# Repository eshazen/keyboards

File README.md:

# Keyboard project(s)

<p>

## Status

All done, working!  Used QMK for the firmware.  
<br>See `my_84/qmk/eric_84/key` for modified
`keyboard.json` and `keymaps/default/keymap.c`.  
<br>See [README_QMK](README_QMK.md).

To change layout, edit `~/qmk_firmware/keyboards/eric_84_key/keymaps/default/keymap.c`.
Then re-flash with:

    qmk flash -kb eric_84_key -km default

(This can be done "live" as long as you have access to the Arduino reset button).

In summary, created the layout in KLE, generated the plate and case
geometry in `swillkb.com`, and the PCB using the `kbplacer` plugin for
KiCAD.  Firmware generated using `qmk`.

Waterjet cutter files for plate in `waterJet`.

## Tools Used:

* [KLE](https://www.keyboard-layout-editor.com)
* [Plate & Case Builder](http://builder.swillkb.com/) (from [github](https://github.com/vladantrhlik/Keyboard_case_generator?tab=readme-ov-file)).  This generates the DXF for the plate and stacked laser-cut case parts.
* [kbplacer plugin](https://github.com/adamws/kicad-kbplacer) for KiCAD layout

## References

* [PCB video](https://www.youtube.com/watch?v=u13yRbBiRYM&t=10s)
* [Case video](https://www.youtube.com/watch?v=NIIr19TdidY)
* [Building Keyboards with Lasers](https://kbd.news/Building-keyboards-with-lasers-2208.html)
* [Keyboard University](https://www.keyboard.university/)
* [Pro Micro up to 100 pins](https://golem.hu/guide/pro-micro/)

Also used 

## My 84 key

<ul>
    [{a:6},"Esc","F1","F2","F3","F4","F5","F6","F7","F8","F9","F10","F11","F12",{a:7},"PrtSc","Shell","Pause"],
    [{a:4},"~\n`","!\n1","@\n2","#\n3","$\n4","%\n5","^\n6","&\n7","*\n8","(\n9",")\n0","_\n-","+\n=",{a:6,w:2},"Backspace",{a:7},"Insert"],
    [{a:4,w:1.5},"Tab","Q","W","E","R","T","Y","U","I","O","P","{\n[","}\n]",{w:1.5},"|\n\\",{a:6},"Delete"],
    [{w:1.75},"Control",{a:4},"A","S","D","F","G","H","J","K","L",":\n;","\"\n'",{a:6,w:2.25},"Enter","Page Up"],
    [{w:2.25},"Shift",{a:4},"Z","X","C","V","B","N","M","<\n,",">\n.","?\n/",{a:6,w:1.75},"Shift",{a:7},"↑",{a:6},"Page Down"],
    [{a:7,w:1.25},"Home",{a:6,w:1.25},"Menu",{w:1.25},"Alt",{a:7,w:6.25},"",{a:6},"Alt","Fn",{a:7},"End","←","↓","→"]

Using [http://builder.swillkb.com/](http://builder.swillkb.com/).

``` text
    Switch type: MX
	Stab:  Cherry + Costar
	Case: Sandwich
	Holes 8, 4.5mm, 10mm
	Edge:  Top: 10, Left: 30, Right: 10, Bottom: 25
	Corners: 2mm
```
<br>DXFs in `...Case/case1`
<br>PCB in `...kb_test`

This was OK except that the opening in the 'top' was a little tight.
Enlarged the CAD file by .05" on all sides.

</ul>

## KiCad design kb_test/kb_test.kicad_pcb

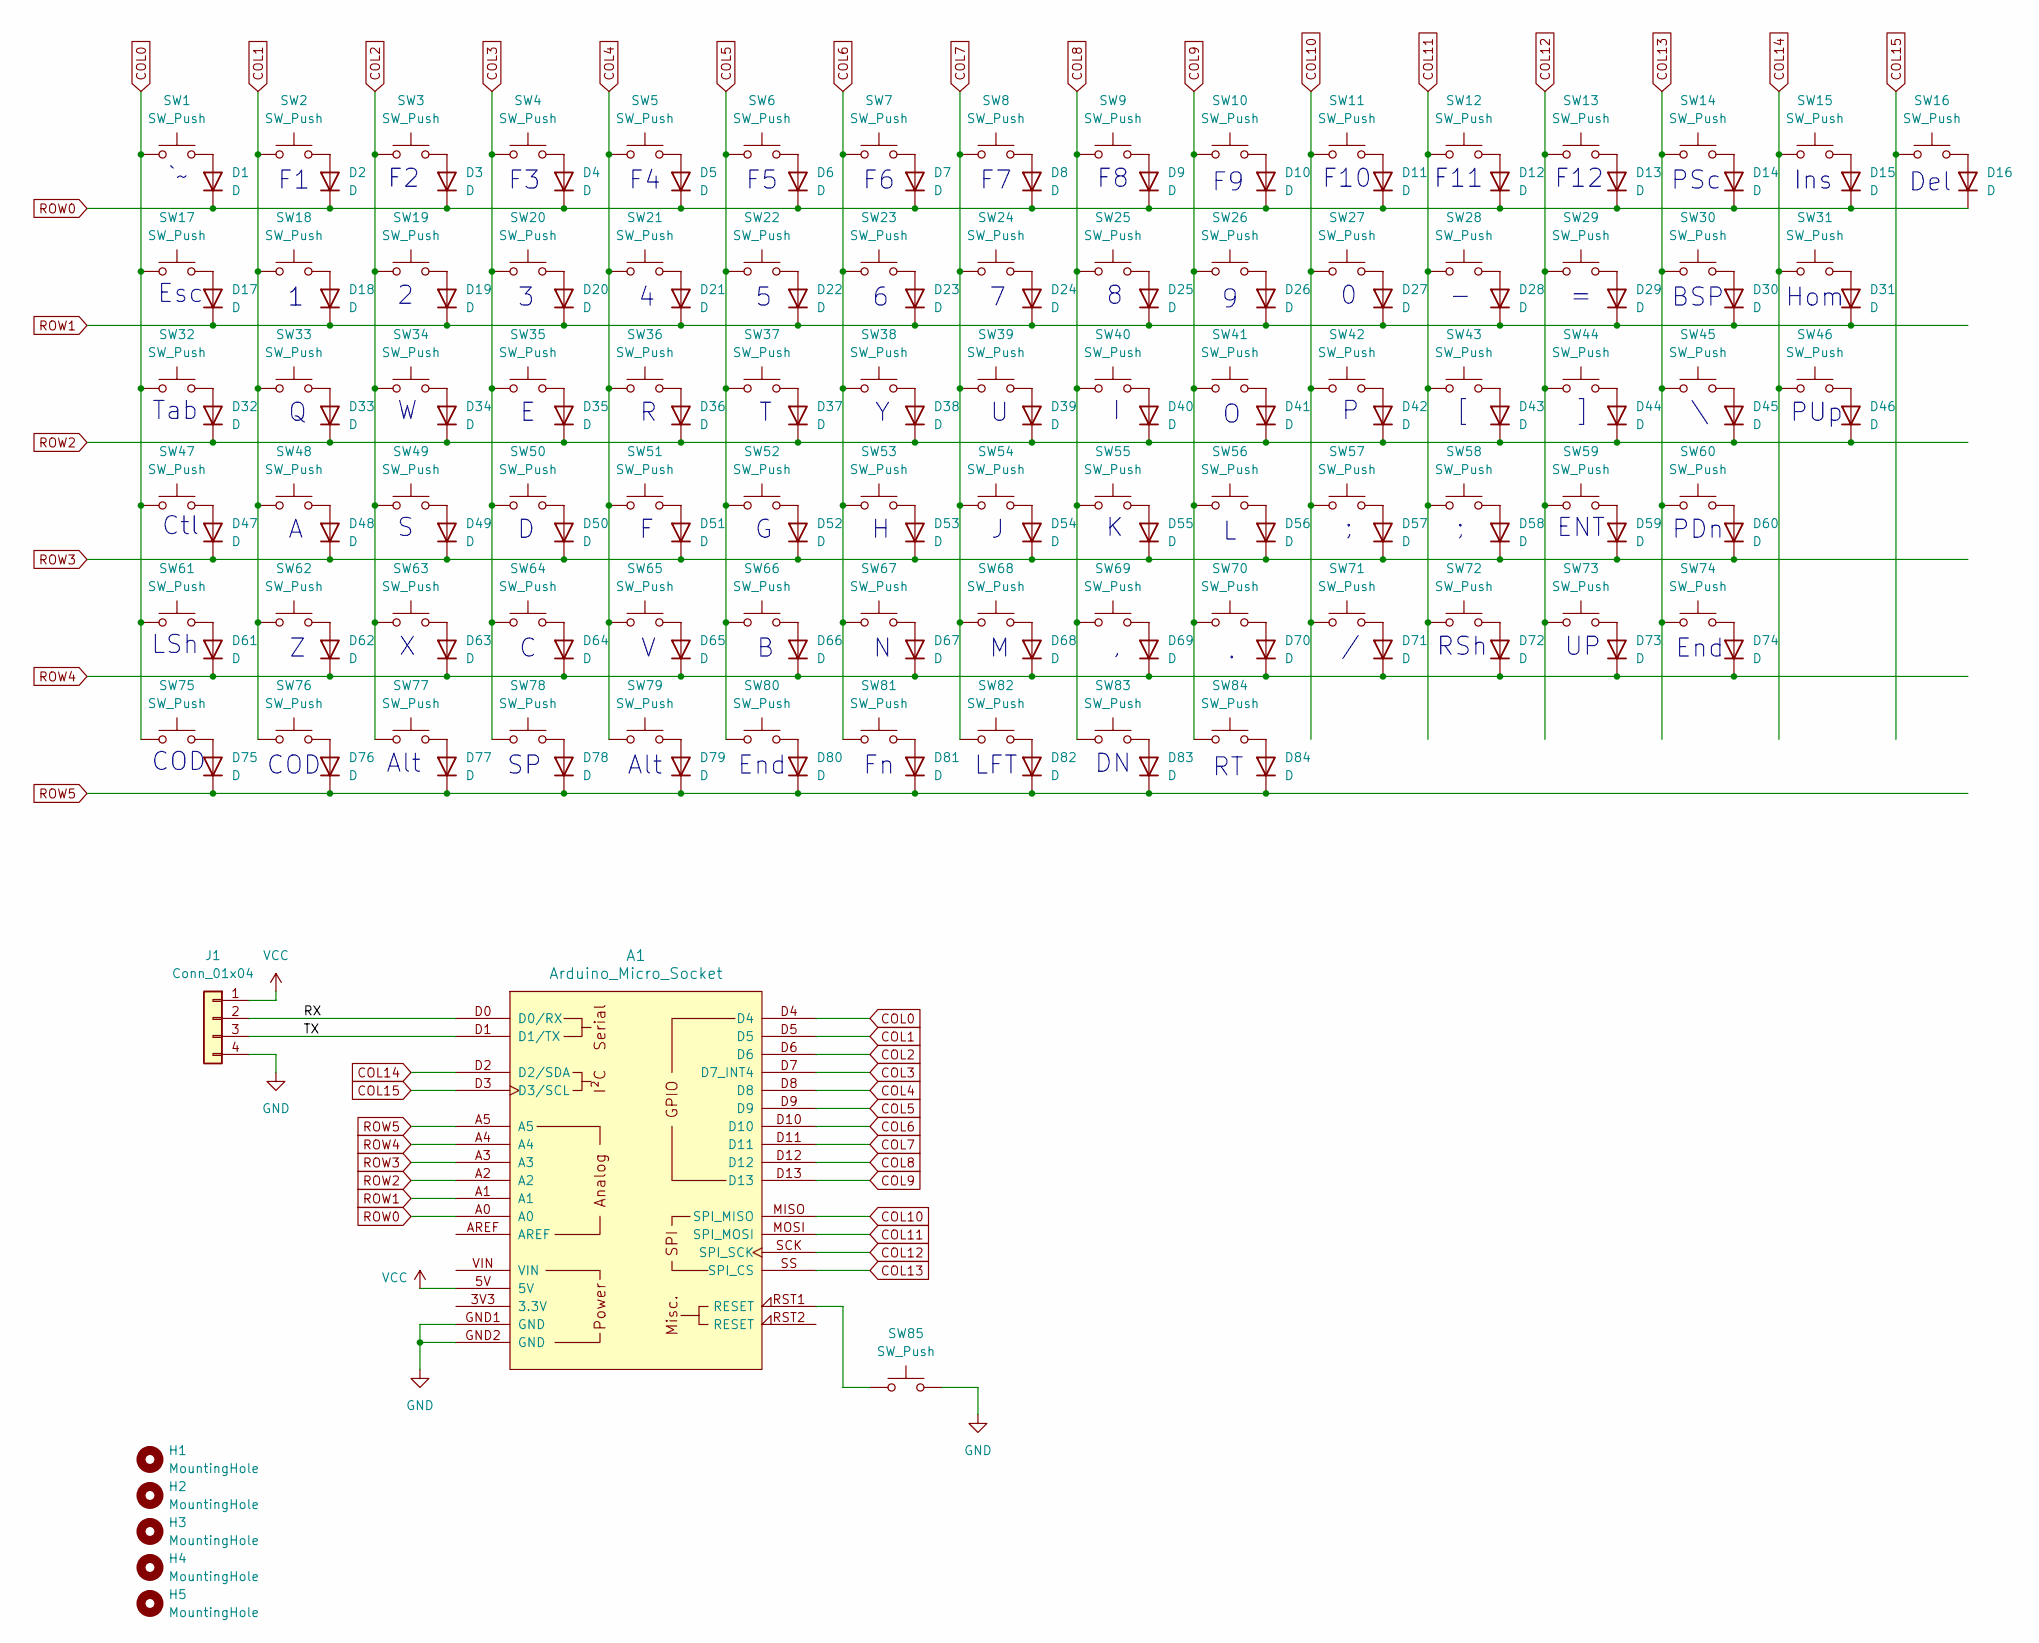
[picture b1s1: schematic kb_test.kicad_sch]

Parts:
A1: Arduino_Micro_Socket
D1, D2, D3, D4, D5, D6, D7, D8, D9, D10, D11, D12, D13, D14, D15, D16, D17, D18, D19, D20, D21, D22, D23, D24, D25, D26, D27, D28, D29, D30, D31, D32, D33, D34, D35, D36, D37, D38, D39, D40, D41, D42, D43, D44, D45, D46, D47, D48, D49, D50, D51, D52, D53, D54, D55, D56, D57, D58, D59, D60, D61, D62, D63, D64, D65, D66, D67, D68, D69, D70, D71, D72, D73, D74, D75, D76, D77, D78, D79, D80, D81, D82, D83, D84: D; D_DO-41_SOD81_P7.62mm_Horizontal
H1, H2, H3, H4, H5: MountingHole; MountingHole_4.3mm_M4
J1: Conn_01x04; PinHeader_1x04_P2.54mm_Vertical
SW1, SW2, SW3, SW4, SW5, SW6, SW7, SW8, SW9, SW10, SW11, SW12, SW13, SW14, SW15, SW16, SW17, SW18, SW19, SW20, SW21, SW22, SW23, SW24, SW25, SW26, SW27, SW28, SW29, SW30, SW31, SW32, SW33, SW34, SW35, SW36, SW37, SW38, SW39, SW40, SW41, SW42, SW43, SW44, SW45, SW46, SW47, SW48, SW49, SW50, SW51, SW52, SW53, SW54, SW55, SW56, SW57, SW58, SW59, SW60, SW61, SW62, SW63, SW64, SW65, SW66, SW67, SW68, SW69, SW70, SW71, SW72, SW73, SW74, SW75, SW76, SW77, SW78, SW79, SW80, SW81, SW82, SW83, SW84: SW_Push; SW_Cherry_MX_1.00u_PCB
SW85: SW_Push; SW_Tactile_Straight_KSA0Axx1LFTR

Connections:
/RX: A1.D0 (D0/RX), J1.2
/TX: A1.D1 (D1/TX), J1.3
COL0: A1.D4, SW1.1, SW17.1, SW32.1, SW47.1, SW61.1, SW75.1
COL1: A1.D5, SW2.1, SW18.1, SW33.1, SW48.1, SW62.1, SW76.1
COL2: A1.D6, SW3.1, SW19.1, SW34.1, SW49.1, SW63.1, SW77.1
COL3: A1.D7 (D7_INT4), SW4.1, SW20.1, SW35.1, SW50.1, SW64.1, SW78.1
COL4: A1.D8, SW5.1, SW21.1, SW36.1, SW51.1, SW65.1, SW79.1
COL5: A1.D9, SW6.1, SW22.1, SW37.1, SW52.1, SW66.1, SW80.1
COL6: A1.D10, SW7.1, SW23.1, SW38.1, SW53.1, SW67.1, SW81.1
COL7: A1.D11, SW8.1, SW24.1, SW39.1, SW54.1, SW68.1, SW82.1
COL8: A1.D12, SW9.1, SW25.1, SW40.1, SW55.1, SW69.1, SW83.1
COL9: A1.D13, SW10.1, SW26.1, SW41.1, SW56.1, SW70.1, SW84.1
COL10: A1.MISO (SPI_MISO), SW11.1, SW27.1, SW42.1, SW57.1, SW71.1
COL11: A1.MOSI (SPI_MOSI), SW12.1, SW28.1, SW43.1, SW58.1, SW72.1
COL12: A1.SCK (SPI_SCK), SW13.1, SW29.1, SW44.1, SW59.1, SW73.1
COL13: A1.SS (SPI_CS), SW14.1, SW30.1, SW45.1, SW60.1, SW74.1
COL14: A1.D2 (D2/SDA), SW15.1, SW31.1, SW46.1
COL15: A1.D3 (D3/SCL), SW16.1
GND: A1.GND1 (GND), A1.GND2 (GND), J1.4, SW85.2
unnamed: A1.RST1 (RESET), SW85.1
unnamed: D1.2 (A), SW1.2
unnamed: D2.2 (A), SW2.2
unnamed: D3.2 (A), SW3.2
unnamed: D4.2 (A), SW4.2
unnamed: D5.2 (A), SW5.2
unnamed: D6.2 (A), SW6.2
unnamed: D7.2 (A), SW7.2
unnamed: D8.2 (A), SW8.2
unnamed: D9.2 (A), SW9.2
unnamed: D10.2 (A), SW10.2
unnamed: D11.2 (A), SW11.2
unnamed: D12.2 (A), SW12.2
unnamed: D13.2 (A), SW13.2
unnamed: D14.2 (A), SW14.2
unnamed: D15.2 (A), SW15.2
unnamed: D16.2 (A), SW16.2
unnamed: D17.2 (A), SW17.2
unnamed: D18.2 (A), SW18.2
unnamed: D19.2 (A), SW19.2
unnamed: D20.2 (A), SW20.2
unnamed: D21.2 (A), SW21.2
unnamed: D22.2 (A), SW22.2
unnamed: D23.2 (A), SW23.2
unnamed: D24.2 (A), SW24.2
unnamed: D25.2 (A), SW25.2
unnamed: D26.2 (A), SW26.2
unnamed: D27.2 (A), SW27.2
unnamed: D28.2 (A), SW28.2
unnamed: D29.2 (A), SW29.2
unnamed: D30.2 (A), SW30.2
unnamed: D31.2 (A), SW31.2
unnamed: D32.2 (A), SW32.2
unnamed: D33.2 (A), SW33.2
unnamed: D34.2 (A), SW34.2
unnamed: D35.2 (A), SW35.2
unnamed: D36.2 (A), SW36.2
unnamed: D37.2 (A), SW37.2
unnamed: D38.2 (A), SW38.2
unnamed: D39.2 (A), SW39.2
unnamed: D40.2 (A), SW40.2
unnamed: D41.2 (A), SW41.2
unnamed: D42.2 (A), SW42.2
unnamed: D43.2 (A), SW43.2
unnamed: D44.2 (A), SW44.2
unnamed: D45.2 (A), SW45.2
unnamed: D46.2 (A), SW46.2
unnamed: D47.2 (A), SW47.2
unnamed: D48.2 (A), SW48.2
unnamed: D49.2 (A), SW49.2
unnamed: D50.2 (A), SW50.2
unnamed: D51.2 (A), SW51.2
unnamed: D52.2 (A), SW52.2
unnamed: D53.2 (A), SW53.2
unnamed: D54.2 (A), SW54.2
unnamed: D55.2 (A), SW55.2
unnamed: D56.2 (A), SW56.2
unnamed: D57.2 (A), SW57.2
unnamed: D58.2 (A), SW58.2
unnamed: D59.2 (A), SW59.2
unnamed: D60.2 (A), SW60.2
unnamed: D61.2 (A), SW61.2
unnamed: D62.2 (A), SW62.2
unnamed: D63.2 (A), SW63.2
unnamed: D64.2 (A), SW64.2
unnamed: D65.2 (A), SW65.2
unnamed: D66.2 (A), SW66.2
unnamed: D67.2 (A), SW67.2
unnamed: D68.2 (A), SW68.2
unnamed: D69.2 (A), SW69.2
unnamed: D70.2 (A), SW70.2
unnamed: D71.2 (A), SW71.2
unnamed: D72.2 (A), SW72.2
unnamed: D73.2 (A), SW73.2
unnamed: D74.2 (A), SW74.2
unnamed: D75.2 (A), SW75.2
unnamed: D76.2 (A), SW76.2
unnamed: D77.2 (A), SW77.2
unnamed: D78.2 (A), SW78.2
unnamed: D79.2 (A), SW79.2
unnamed: D80.2 (A), SW80.2
unnamed: D81.2 (A), SW81.2
unnamed: D82.2 (A), SW82.2
unnamed: D83.2 (A), SW83.2
unnamed: D84.2 (A), SW84.2
ROW0: A1.A0, D1.1 (K), D2.1 (K), D3.1 (K), D4.1 (K), D5.1 (K), D6.1 (K), D7.1 (K), D8.1 (K), D9.1 (K), D10.1 (K), D11.1 (K), D12.1 (K), D13.1 (K), D14.1 (K), D15.1 (K), D16.1 (K)
ROW1: A1.A1, D17.1 (K), D18.1 (K), D19.1 (K), D20.1 (K), D21.1 (K), D22.1 (K), D23.1 (K), D24.1 (K), D25.1 (K), D26.1 (K), D27.1 (K), D28.1 (K), D29.1 (K), D30.1 (K), D31.1 (K)
ROW2: A1.A2, D32.1 (K), D33.1 (K), D34.1 (K), D35.1 (K), D36.1 (K), D37.1 (K), D38.1 (K), D39.1 (K), D40.1 (K), D41.1 (K), D42.1 (K), D43.1 (K), D44.1 (K), D45.1 (K), D46.1 (K)
ROW3: A1.A3, D47.1 (K), D48.1 (K), D49.1 (K), D50.1 (K), D51.1 (K), D52.1 (K), D53.1 (K), D54.1 (K), D55.1 (K), D56.1 (K), D57.1 (K), D58.1 (K), D59.1 (K), D60.1 (K)
ROW4: A1.A4, D61.1 (K), D62.1 (K), D63.1 (K), D64.1 (K), D65.1 (K), D66.1 (K), D67.1 (K), D68.1 (K), D69.1 (K), D70.1 (K), D71.1 (K), D72.1 (K), D73.1 (K), D74.1 (K)
ROW5: A1.A5, D75.1 (K), D76.1 (K), D77.1 (K), D78.1 (K), D79.1 (K), D80.1 (K), D81.1 (K), D82.1 (K), D83.1 (K), D84.1 (K)
VCC: A1.5V, J1.1

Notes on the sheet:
PUp
End
Alt
Del
LSh
LFT
ENT
PSc
F12
Hom
COD
BSP
F11
RSh
Ctl
PDn
Tab
Esc
F10
Ins

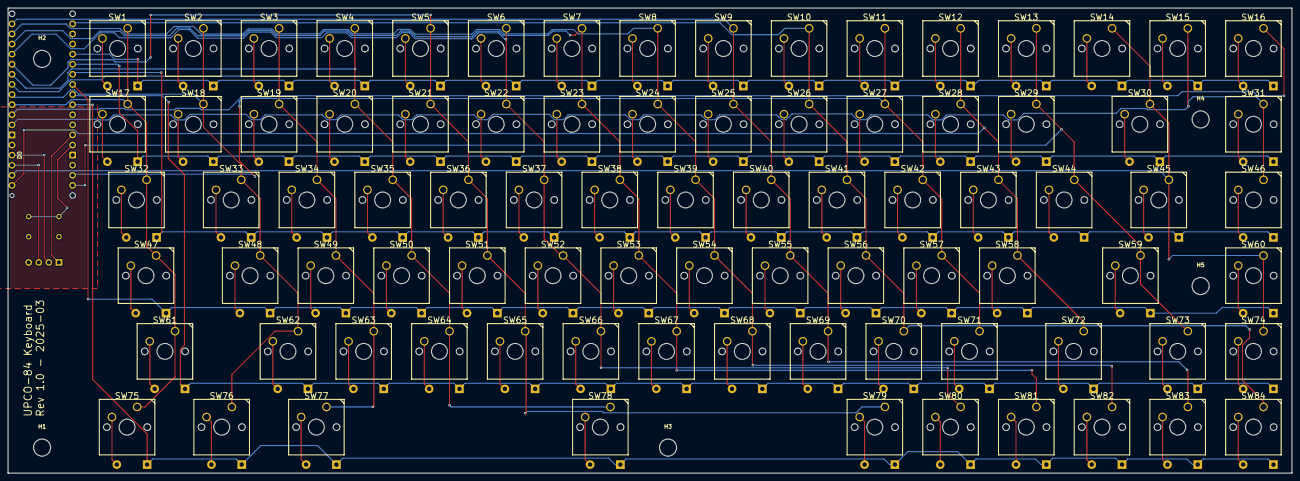
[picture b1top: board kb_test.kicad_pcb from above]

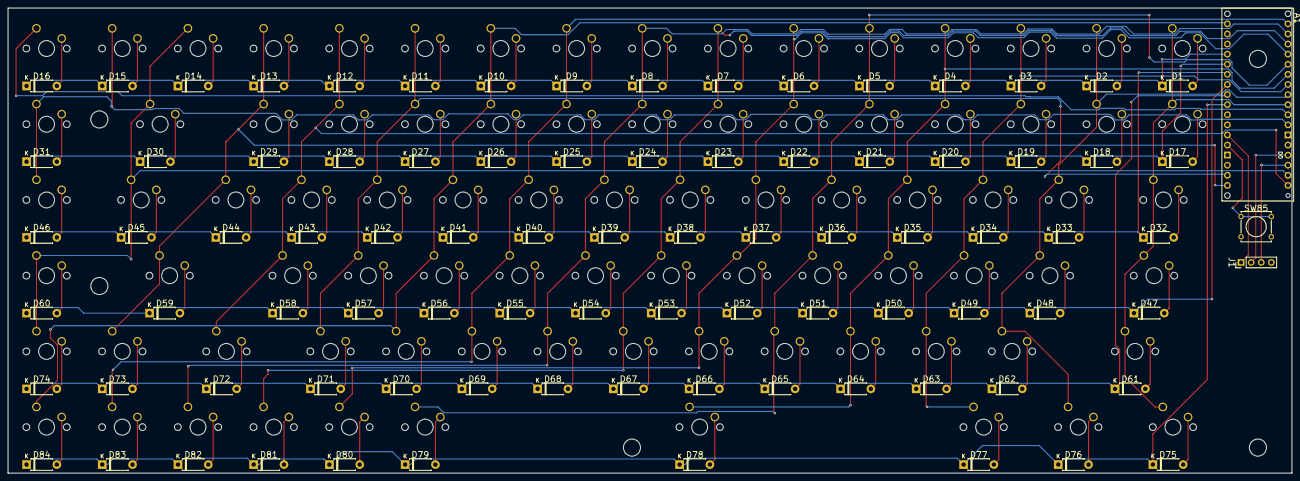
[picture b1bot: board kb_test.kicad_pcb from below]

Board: 2 copper layers, 323.0 x 117.0 mm, 176 parts (87 on the bottom side), 111 nets.

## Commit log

2025-03-04 test version of 84 key
2025-03-08 readme
2025-03-09 Tentative placement with diodes on front
2025-03-09 clean up
2025-03-09 candidate placement with diodes and MCU on bottom
2025-03-09 tentative placement with simple MX models
2025-03-10 working on case
2025-03-12 Update 'shrink' option, fix joint issues
2025-03-12 prelim gerbers
2025-03-23 Hardware as built; QMK firmware config OK
2025-03-27 tweak plates
2025-03-28 save qmk config
2025-04-01 update a few things, add waterjet files
2025-04-03 Readme QMK
2025-04-07 top with missing home key
2025-04-08 start portable
2025-04-08 cleaning up
